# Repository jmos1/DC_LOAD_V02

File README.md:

# DC_LOAD_V02

### Summary: ###
  This board is a follow up to the 1A DC_LOAD_V01 prototype. It is a 5A, 30V, 100W constant current load that will be mounted
  in a Jameco project enclosure. It currently isn't finished or tested yet, but feel free to have a look around anyway!

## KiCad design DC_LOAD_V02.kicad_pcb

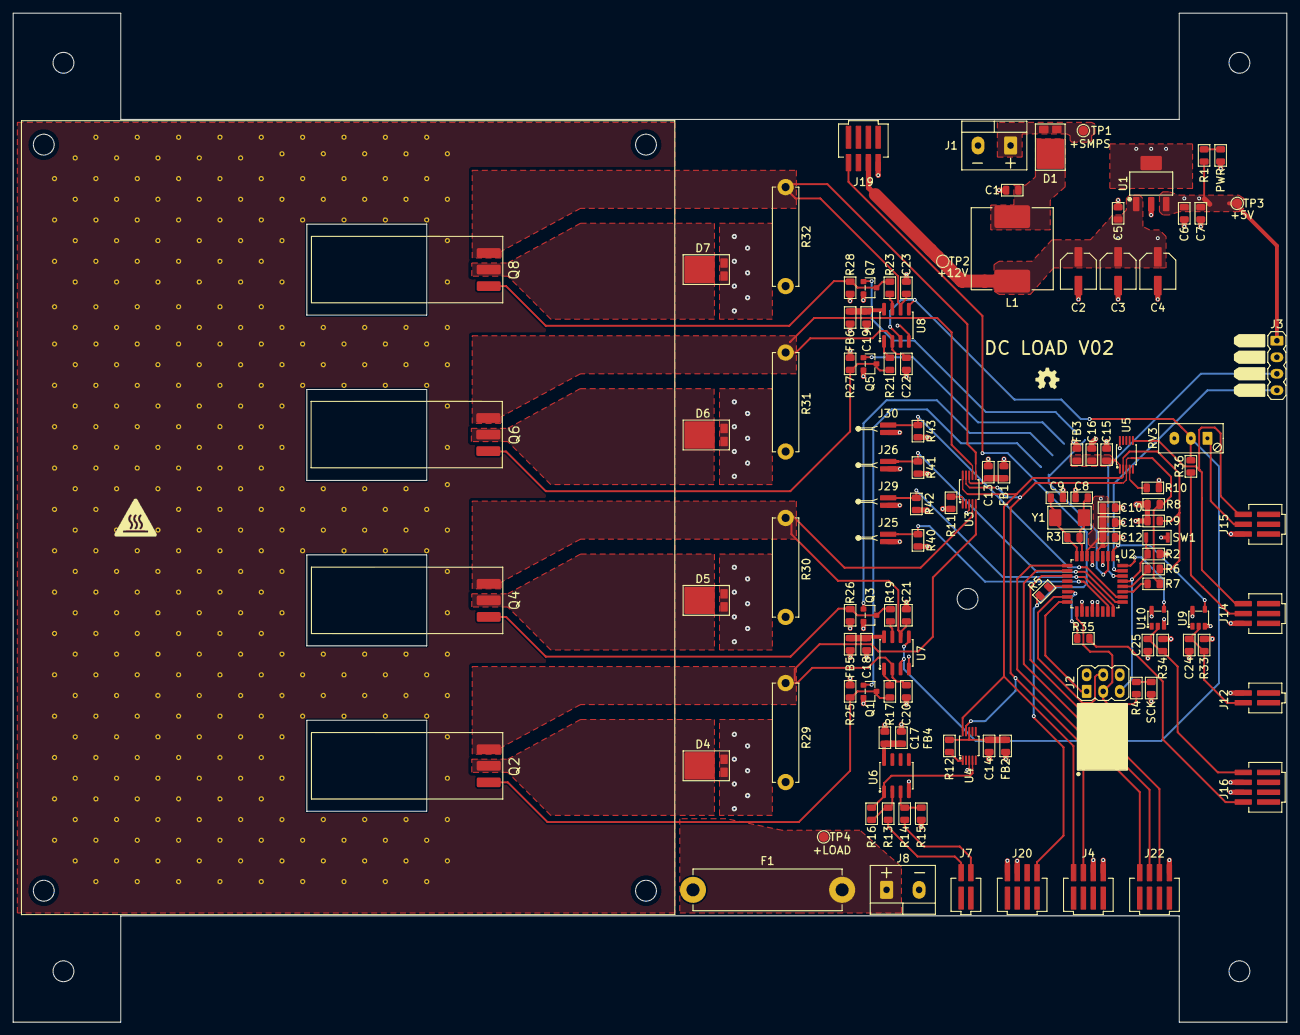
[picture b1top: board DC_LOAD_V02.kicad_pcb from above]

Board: 4 copper layers, 195.6 x 154.9 mm, 131 parts (0 on the bottom side), 75 nets.

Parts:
C1, C15, C20, C21, C22, C23: 10u, 25V; 0805_2012Metric_Reflow
C2, C3, C4: 22u, 35V; CP_Elec_5x5.8
C5, C6, C10, C13, C14, C24, C25: 1u, 50V; 0805_2012Metric_Reflow
C7, C11, C16, C18, C19: 100n, 50V; 0805_2012Metric_Reflow
C8, C9: 18p, 50V; 0805_2012Metric_Reflow
C12, C17: 10n, 50V; 0805_2012Metric_Reflow
D1, D4, D5, D6, D7: FSV8100V
F1: 5A; Fuse_Holder_5x20mm_3527
FB1, FB2, FB3, FB4, FB5, FB6: MI0805L301R-10; 0805_2012Metric_Reflow
H1, H2, H3, H4, H5, H6, H7, H8, H9: MountingHole; MountingHole_3.2mm_M3
J1, J8: Screw_Terminal_01x02; Conn_Term_2POS_5mm_PITCH_691137710002
J2: Conn_02x03_Odd_Even; Conn_Header_Male_2x3_2.54mm_PITCH
J3: Conn_01x04; Conn_Header_Male_1x4_2.54mm_PITCH
J4, J16, J19, J20, J22: Conn_01x04; Conn_Molex_1x4_Horizontal_1.5mm_Pitch_0874380443
J7, J12: Conn_01x02; Conn_Molex_1x2_Horizontal_1.5mm_Pitch_0874380243
J14, J15: Conn_01x03; Conn_Molex_1x3_Horizontal_1.5mm_Pitch_0874380343
J25, J26, J29, J30: Conn_01x02; Therm_Pad
L1: 100u; 49101SC
PWR: GRN; 0805_2012Metric_Reflow
Q1, Q3, Q5, Q7: MMBT3904LT3G; SOT-23
Q2, Q4, Q6, Q8: STP80NF55L-06
R1, R4, R10, R17, R18, R19, R20, R21, R22, R23, R24, R25, R26, R27, R28, R35: 1KR; 0805_2012Metric_Reflow
R2, R8, R9, R11, R15, R16, R33, R34, R36, R40, R41, R42, R43: 10KR; 0805_2012Metric_Reflow
R3: 1M; 0805_2012Metric_Reflow
R5, R6, R7: 0R; 0805_2012Metric_Reflow
R12: 0R0; 0805_2012Metric_Reflow
R13, R14: 100KR; 0805_2012Metric_Reflow
R29, R30, R31, R32: 0R1; R_Radial_0R1_Riedon_MSR3
RV3: 50KR_TRIM; Pot_Trim_THT_9.5mmx4.35mm
SCK: YEL; 0805_2012Metric_Reflow
SW1: EVP-AWED2A
TP1, TP2, TP3, TP4: TestPoint; TestPoint_Pad_D1.5mm
U1: LM7805MPX/NOPB; SOT-223
U2: ATMEGA328P; TQFP-32_7x7mm_P0.8mm
U3, U4: ADS1115IDGSR; VSSOP-10_.5mm_PITCH_3x3mm_PKG
U5: MCP4728T-E/UN; MSOP-10_3x3mm_P0.5mm
U6: LM6132; SOIC-8_3.9x4.9mm_P1.27mm
U7, U8: LM358DR; SOIC-8_3.9x4.9mm_P1.27mm
U9, U10: NC7S14M5X; SOT-23-5
Y1: ABM7-16.000MHZ-D2Y-T

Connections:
328P_ADC0: J25.1, R40.2, U2.23
328P_ADC1: J29.1, R42.2, U2.24
328P_ADC2: J26.1, R41.2, U2.25
328P_ADC3: J30.1, R43.2, U2.26
328P_PB2: R35.2, U2.14
328P_PD2: U2.32, U10.4
328P_PD3: U2.1, U9.4
328P_PD4: R18.2, R20.1, R22.1, R24.1, U2.2
328P_PD5: J22.1, U2.9
328P_PD6: J22.2, U2.10
328P_PD7: J22.3, U2.11
+5V: C6.1, C7.1, C10.1, C11.1, C12.1, FB1.2, FB2.2, FB3.2, J2.2, J3.1, J4.3, R1.1, R2.1, R8.1, R9.1, R33.1, R34.1, R40.1, R41.1, R42.1, R43.1, TP3.1, U1.3, U2.4, U2.6, U2.18, U2.20, U9.5, U10.5
+12V: C2.1, C3.1, C4.1, C5.1, C20.1, C21.1, C22.1, C23.1, FB4.1, FB5.1, FB6.1, J19.2, J20.2, L1.2, TP2.1, U1.1
/Current Control and Vsense/358_OUT1: R17.1, U7.1
/Current Control and Vsense/358_OUT2: R19.1, U7.7
/Current Control and Vsense/358_OUT3: R21.1, U8.1
/Current Control and Vsense/358_OUT4: R23.1, U8.7
/Current Control and Vsense/+LM358_VCC1: C18.1, FB5.2, U7.8
/Current Control and Vsense/+LM358_VCC2: C19.1, FB6.2, U8.8
/Current Control and Vsense/+LM6132_VCC: C17.1, FB4.2, U6.8
/Current Control and Vsense/+LOAD: F1.2, J8.1, TP4.1
/Current Control and Vsense/+LOAD_FUSED: D4.1, D4.2, D5.1, D5.2, D6.1, D6.2, D7.1, D7.2, F1.1
/Current Control and Vsense/BASE1: Q1.1, R18.1
/Current Control and Vsense/BASE2: Q3.1, R20.2
/Current Control and Vsense/BASE3: Q5.1, R22.2
/Current Control and Vsense/BASE4: Q7.1, R24.2
/Current Control and Vsense/GATE1: Q1.3, Q2.1, R17.2, R25.1
/Current Control and Vsense/GATE2: Q3.3, Q4.1, R19.2, R26.1
/Current Control and Vsense/GATE3: Q5.3, Q6.1, R21.2, R27.1
/Current Control and Vsense/GATE4: Q7.3, Q8.1, R23.2, R28.1
/Current Control and Vsense/LM6132+: R14.2, R15.1, U6.3
/Current Control and Vsense/LM6132-: R13.2, R16.1, U6.2
/Power/+SMPS_OUT: D1.1, D1.2, J1.1, TP1.1
/Processing/328P_MISO: J2.1, U2.16
/Processing/328P_MOSI: J2.4, U2.15
/Processing/328P_OC1A: R5.1, U2.13
/Processing/328P_RST: J2.5, R2.2, SW1.2, U2.29
/Processing/328P_RX: J3.3, U2.30
/Processing/328P_SCK: J2.3, R4.2, U2.17
/Processing/328P_SCL: R6.1, U2.28
/Processing/328P_SDA: R7.1, U2.27
/Processing/328P_TX: J3.4, U2.31
/Processing/328P_XTAL1: C8.2, R3.1, U2.7, Y1.2
/Processing/328P_XTAL2: C9.2, R3.2, U2.8, Y1.1
/Processing/+ADS_VDD1: C13.1, FB1.1, U3.8
/Processing/+ADS_VDD2: C14.1, FB2.1, R12.1, U4.8
/Processing/+MCP_VDD: C15.1, C16.1, FB3.1, U5.1
/Processing/ADS_ADDR1: R11.1, U3.1
/Processing/ADS_ADDR2: R12.2, U4.1
/Processing/MCP_LDAC: R10.1, U5.4
/Processing/SCL_R: J4.1, R6.2, R9.2, U3.10, U4.10, U5.2
/Processing/SDA_R: J4.2, R7.2, R8.2, U3.9, U4.9, U5.3
/Sensors and Mechanical/LOAD_BTN: C25.1, J16.4, R34.2, U10.2
/Sensors and Mechanical/SCREEN_BTN: C24.2, J12.1, R33.2, U9.2
ADC_VLOAD0: R16.2, U4.4, U6.1
DAC_VOUTA: J14.3, J15.3, U5.6
GND: C1.2, C2.2, C3.2, C4.2, C5.2, C6.2, C7.2, C8.1, C9.1, C10.2, C11.2, C12.2, C13.2, C14.2, C15.2, C16.2, C17.2, C18.2, C19.2, C24.1, C25.2, J1.2, J2.6, J3.2, J4.4, J8.2, J12.2, J14.1, J15.1, J16.2, J16.3, J19.1, J20.1, J22.4, J25.2, J26.2, J29.2, J30.2, PWR.1, Q1.2, Q3.2, Q5.2, Q7.2, R10.2, R11.2, R15.2, R25.2, R26.2, R27.2, R28.2, R29.2, R30.2, R31.2, R32.2, SCK.1, SW1.1, U1.2, U1.4, U2.3, U2.5, U2.21, U3.3, U4.3, U5.10, U6.4, U7.4, U8.4, U9.3, U10.3
LM358+: R36.2, RV3.2, U7.3, U7.5, U8.3, U8.5
unnamed: C1.1, D1.3, L1.1
unnamed: PWR.2, R1.2
unnamed: R4.1, SCK.2
unnamed: D4.3, Q2.2
unnamed: D5.3, Q4.2
unnamed: D6.3, Q6.2
unnamed: D7.3, Q8.2
unnamed: J7.1, R13.1
unnamed: J7.2, R14.1
unnamed: J14.2, R36.1
unnamed: J15.2, RV3.1
unnamed: J16.1, R35.1
PWM_FAN: J19.4, J20.4, R5.2
SHUNT1+: C20.2, Q2.3, R29.1, U3.5, U7.2
SHUNT2+: C21.2, Q4.3, R30.1, U3.4, U7.6
SHUNT3+: C22.2, Q6.3, R31.1, U3.7, U8.2
SHUNT4+: C23.2, Q8.3, R32.1, U3.6, U8.6

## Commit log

2020-09-18 First Push
